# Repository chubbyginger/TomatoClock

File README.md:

# TomatoClock
自制番茄钟

## 介绍

现在市面上的番茄钟都很贵，因此打算自己做一个。

### 功能

1. 可以实现基本的番茄钟功能（计时）和到时提醒。
2. 这是一个特别功能，包含一个超声波传感器。将传感器正对着人体，如果在工作时离开了书桌，那么传感器检测到距离将会变大，将会触发一个惩罚机制，番茄钟会通过升压电路将电压升到60伏左右，释放给人体，使人疼痛，达到惩罚效果。
3. 可以查看学习情况（如离开座位几次等）

### 硬件方案

* 主控芯片：STM32F103C8T6 at 72MHz
* 屏幕：SSD1306 (I2C)
* 超声波模块：HC-SR04
* 目前版本没有升压电路。

目前所有的硬件方案都在Hardware文件夹下保存。每一个版本都会有PCB。

外壳将会考虑使用3D打印件。

### 软件方案

原本是要用Atmel的ATmega328的8位主控的，但后来发现内存太小，因此换用了STM32，用ST官方推荐的CubeIDE开发。

## 开源协议

本项目采用`GPL v3`协议（详见LICENSE文件）。

近期有很多人的开源项目遭到了无良商家的滥用，没有遵循原有的开源协议，这不仅是非常恶心的行为，同时也是违法的。对于这类行为，我们是要强烈抵制的。

在这里务必提醒，如果有人需要用我的程序，是完全没有问题的，但是务必要使用GPL协议开源，并且要说明原作者名字。

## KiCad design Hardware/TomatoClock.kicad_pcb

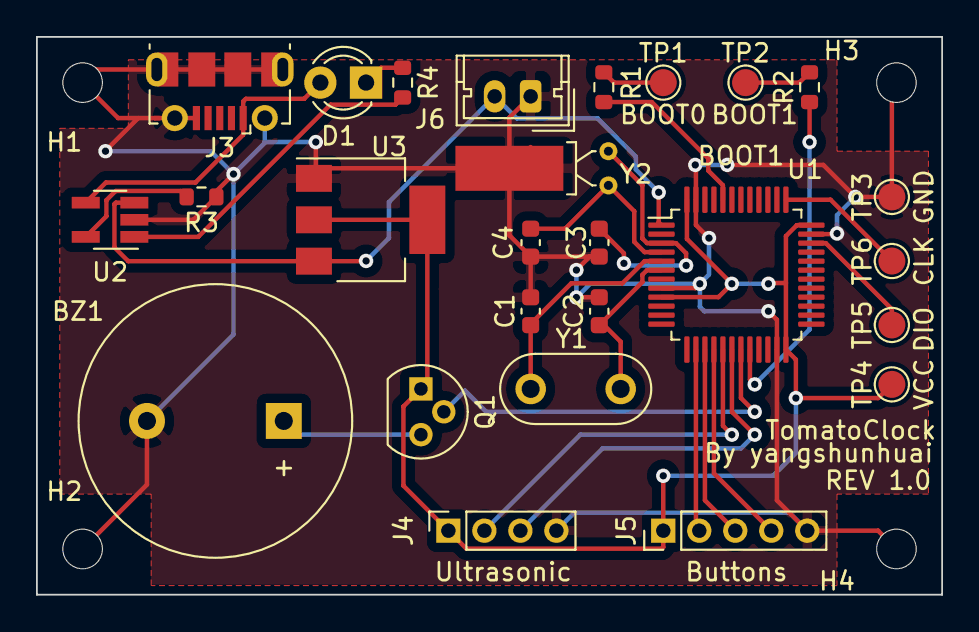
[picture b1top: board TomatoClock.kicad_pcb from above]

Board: 2 copper layers, 50.3 x 31.0 mm, 30 parts (0 on the bottom side), 24 nets.

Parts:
BZ1: Buzzer; Buzzer_15x7.5RM7.6
C1, C2, C3, C4: 22pF; C_0603_1608Metric
D1: Charge; LED_D3.0mm
H1, H2, H3, H4: hole; MountingHole_2.2mm_M2
J3: USB_B_Micro; USB_Micro-B_Molex-105017-0001
J4: Ultrasonic; PinSocket_1x04_P2.00mm_Vertical
J5: Buttons; PinHeader_1x05_P2.00mm_Vertical
J6: Battery; Molex_Micro-Latch_53253-0270_1x02_P2.00mm_Vertical
Q1: S9014; TO-92
R1, R2: 100k; R_0603_1608Metric
R3, R4: 10k; R_0603_1608Metric
TP1: BOOT0; TestPoint_Pad_D1.5mm
TP2: BOOT1; TestPoint_Pad_D1.5mm
TP3: GND; TestPoint_Pad_D1.5mm
TP4: VCC; TestPoint_Pad_D1.5mm
TP5: SWDIO; TestPoint_Pad_D1.5mm
TP6: SWCLK; TestPoint_Pad_D1.5mm
U1: STM32F103C8T6; LQFP-48_7x7mm_P0.5mm
U2: WS4518E; SOT-23-5_HandSoldering
U3: AP1117-33; SOT-223-3_TabPin2
Y1: 8MHz; Resonator-2Pin_W8.0mm_H3.5mm
Y2: 32.768kHz; Crystal_DS26_D2.0mm_L6.0mm_Horizontal_1EP_style1

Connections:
+3V3: J4.1, J5.1, Q1.1, TP4.1, U1.9, U1.24, U1.36, U1.48, U3.2
+BATT: J6.2, U1.1, U2.3, U3.3
BOOT0: R1.2, TP1.1
BOOT1: R2.2, TP2.1
BUZZER: Q1.2, U1.19
GND: BZ1.2, C1.2, C2.2, C3.2, C4.2, H1.1, H2.1, H3.1, H4.1, J3.5, J3.6, J4.4, J5.5, J6.1, R3.1, TP3.1, U1.8, U1.23, U1.35, U1.47, U2.2, U3.1, Y2.3
LEFT: J5.2, U1.14
MIDDLE: J5.3, U1.15
unnamed: BZ1.1, Q1.3
unnamed: C1.1, U1.5, Y1.1
unnamed: C2.1, U1.6, Y1.2
unnamed: C3.1, U1.3, Y2.1
unnamed: C4.1, U1.4, Y2.2
unnamed: D1.1, R4.1
unnamed: R1.1, U1.44
unnamed: R2.1, U1.20
unnamed: R3.2, U2.5
unnamed: R4.2, U2.1
RIGHT: J5.4, U1.16
SWCLK: TP6.1, U1.37
SWDIO: TP5.1, U1.34
US_ECHO: J4.3, U1.18
US_TRIG: J4.2, U1.17
VBUS: D1.2, J3.1, U2.4

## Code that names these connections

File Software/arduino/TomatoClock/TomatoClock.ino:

/*
 * TomatoClock Main Program
 * Wiring: See hardware schematics
 * Author: yangshunhuai
 * Revision: 1.0
 */

#include <U8g2lib.h>
#include <OneButton.h>
#include "tones.h"

// Device pins
#define BTNLEFT    PA4
#define BTNENTER   PA5
#define BTNRIGHT   PA6
#define BUZZER     PB1
#define US_TRIG    PA7
#define US_ECHO    PB0

// Devices
U8G2_SSD1306_128X64_NONAME_F_HW_I2C u8g2(U8G2_R0, /* reset=*/ U8X8_PIN_NONE);
OneButton btnleft(BTNLEFT, false);
OneButton btnenter(BTNENTER, false);
OneButton btnright(BTNRIGHT, false);

void setup() {
  // Configure pins
  pinMode(BUZZER, OUTPUT);
  pinMode(US_TRIG, OUTPUT);
  pinMode(US_ECHO, INPUT);
  // Configure devices
  u8g2.begin();
}

void loop() {
  // put your main code here, to run repeatedly:
  tone(BUZZER, 1000, 20);
}

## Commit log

2021-12-18 Moving all the files here
2021-12-18 Software: Add Keil MDK empty project
2021-12-19 Hardware: Update PCB and schematics
2021-12-25 Update Git Ignore
2021-12-25 Hardware: Update hardware
2021-12-25 Software: Remove keil-mdk and add cubeide projects
2022-01-22 A lot of update
2022-01-23 Remove unnecessary files
2022-01-24 Add RTC files
2022-01-26 LICENSE: Change to GPL v3
2022-01-26 Update gitignore
2022-01-27 Update RTC code
2022-01-28 Create LICENSE
2022-03-12 Add copper layer
